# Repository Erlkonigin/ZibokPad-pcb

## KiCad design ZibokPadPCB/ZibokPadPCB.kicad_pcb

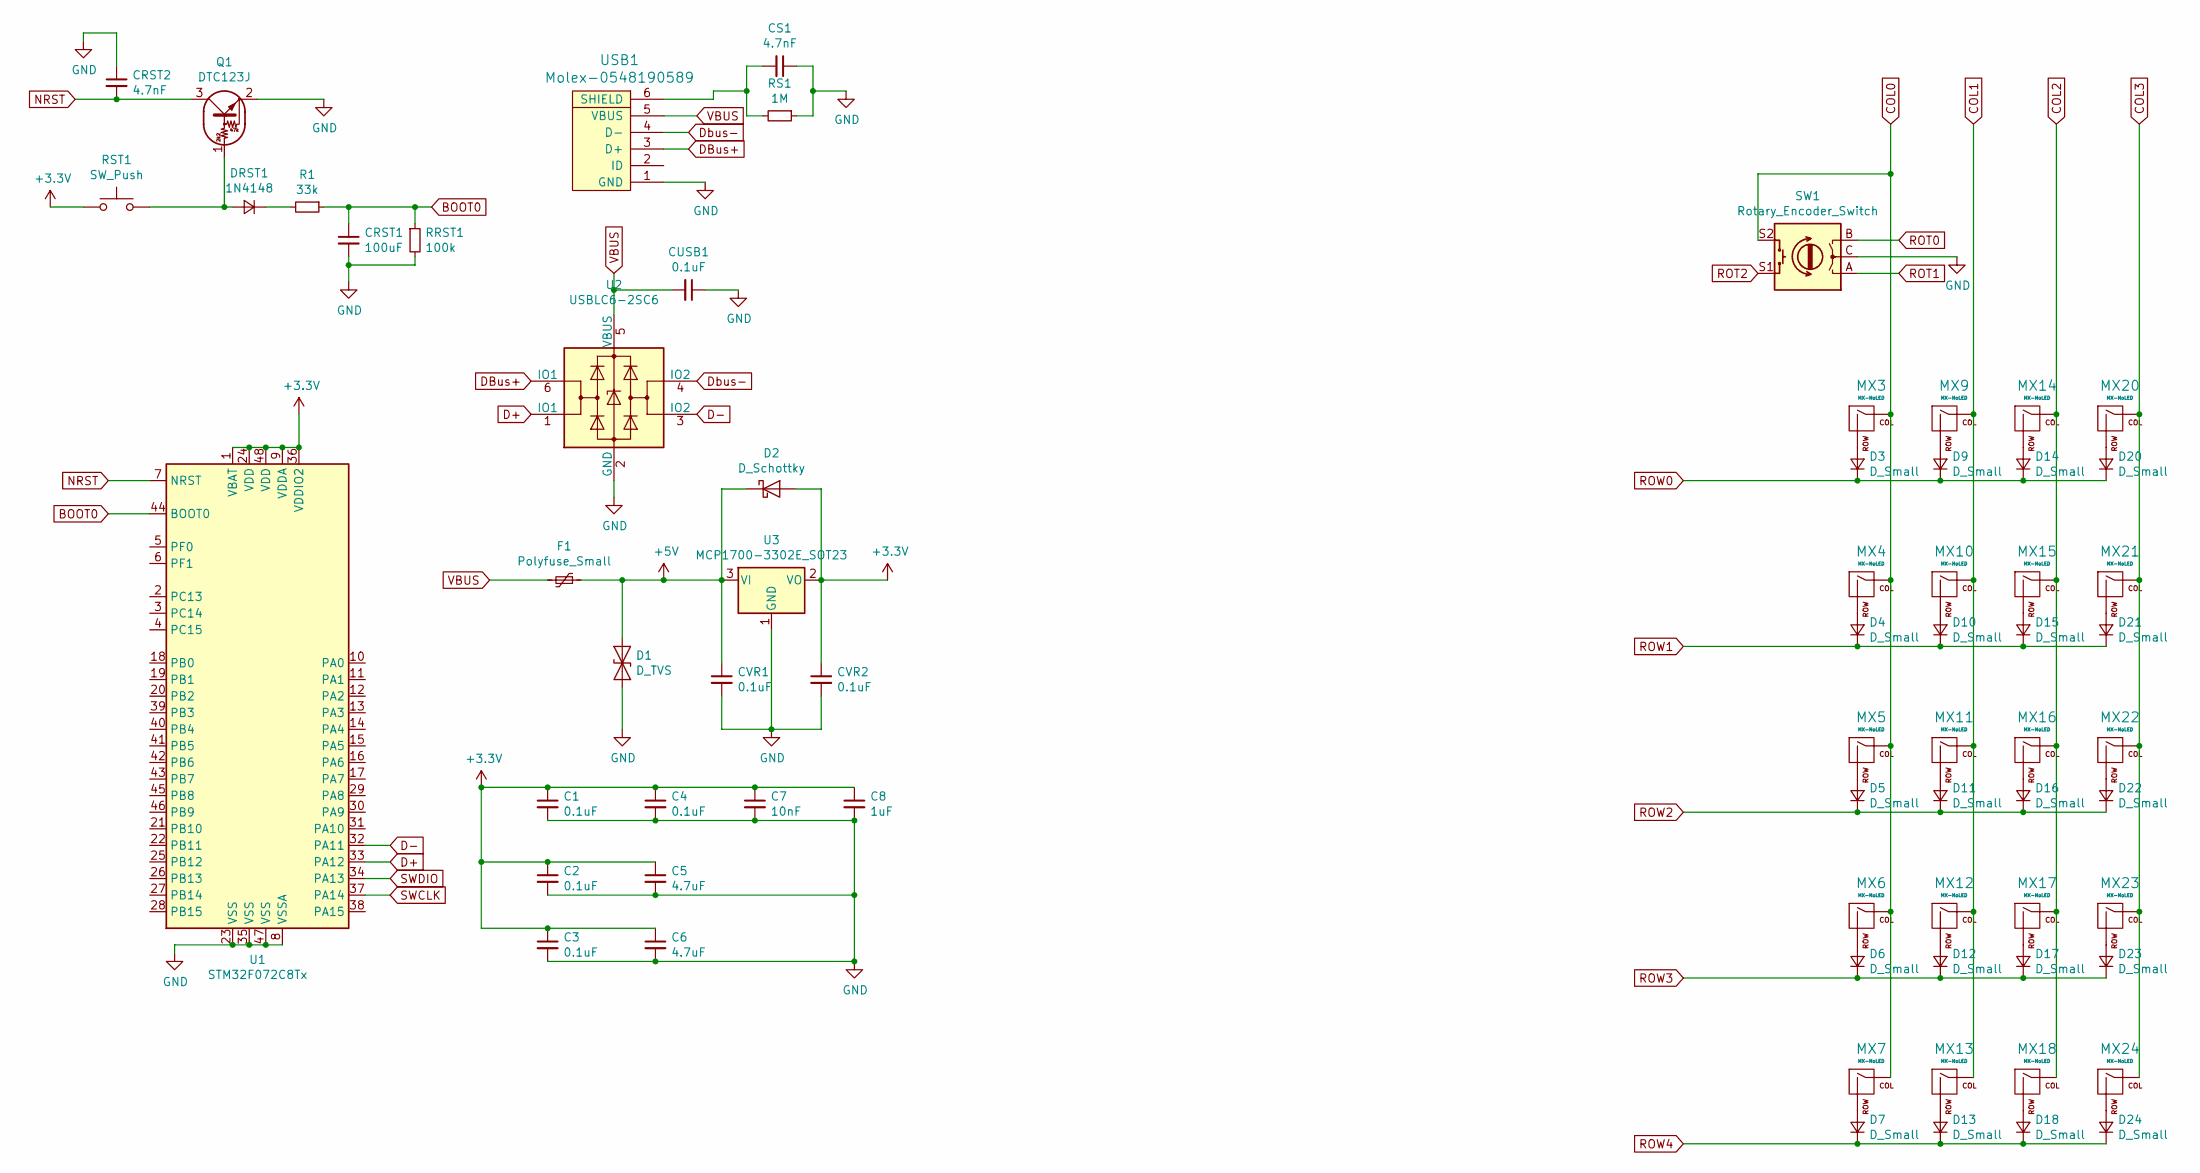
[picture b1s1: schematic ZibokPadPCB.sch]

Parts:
C1, C2, C3, C4: 0.1uF; C_0805_2012Metric
C5, C6: 4.7uF; C_0805_2012Metric
C7: 10nF; C_0805_2012Metric
C8: 1uF; C_0805_2012Metric
CRST1: 100uF; C_0805_2012Metric
CRST2: 4.7nF; C_0805_2012Metric
CS1: 4.7nF; C_0805_2012Metric
CUSB1: 0.1uF; C_0805_2012Metric
CVR1, CVR2: 0.1uF; C_0805_2012Metric
D1: D_TVS; D_SOD-123
D2: D_Schottky; D_SOD-123
D3, D4, D5, D6, D7, D9, D10, D11, D12, D13, D14, D15, D16, D17, D18, D20, D21, D22, D23, D24: D_Small; D_SOD-123
DRST1: 1N4148; D_SOD-123
F1: Polyfuse_Small; Fuse_1206_3216Metric
MX3, MX4, MX5, MX6, MX7, MX9, MX10, MX11, MX12, MX13, MX14, MX15, MX16, MX17, MX18, MX20, MX21, MX22, MX23, MX24: MX-NoLED; MXOnly-1U-NoLED
Q1: DTC123J; SOT-523
R1: 33k; R_0805_2012Metric
RRST1: 100k; R_0805_2012Metric
RS1: 1M; R_0805_2012Metric
RST1: SW_Push; SKQG-1155865
SW1: Rotary_Encoder_Switch; RotaryEncoder_Alps_EC11E-Switch_Vertical_H20mm
U1: STM32F072C8Tx; LQFP-48_7x7mm_P0.5mm
U2: USBLC6-2SC6; SOT-23-6
U3: MCP1700-3302E_SOT23; SOT-23
USB1: Molex-0548190589

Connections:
+3V3: C1.1, C2.1, C3.1, C4.1, C5.1, C6.1, C7.1, C8.1, CVR2.1, D2.2 (A), RST1.1, U1.1 (VBAT), U1.9 (VDDA), U1.24 (VDD), U1.36 (VDDIO2), U1.48 (VDD), U3.2 (VO)
+5V: CVR1.1, D1.1 (A1), D2.1 (K), F1.1, U3.3 (VI)
BOOT0: CRST1.1, R1.1, RRST1.1, U1.44 (BOOT0)
COL0: MX3.1 (COL), MX4.1 (COL), MX5.1 (COL), MX6.1 (COL), MX7.1 (COL), SW1.S2, U1.22 (PB11)
COL1: MX9.1 (COL), MX10.1 (COL), MX11.1 (COL), MX12.1 (COL), MX13.1 (COL), U1.21 (PB10)
COL2: MX14.1 (COL), MX15.1 (COL), MX16.1 (COL), MX17.1 (COL), MX18.1 (COL), U1.20 (PB2)
COL3: MX20.1 (COL), MX21.1 (COL), MX22.1 (COL), MX23.1 (COL), MX24.1 (COL), U1.19 (PB1)
D+: U1.33 (PA12), U2.1 (IO1)
D-: U1.32 (PA11), U2.3 (IO2)
DBus+: U2.6 (IO1), USB1.3 (D+)
Dbus-: U2.4 (IO2), USB1.4 (D-)
GND: C1.2, C2.2, C3.2, C4.2, C5.2, C6.2, C7.2, C8.2, CRST1.2, CRST2.1, CS1.1, CUSB1.1, CVR1.2, CVR2.2, D1.2 (A2), Q1.2 (E), RRST1.2, RS1.1, SW1.C, U1.8 (VSSA), U1.23 (VSS), U1.35 (VSS), U1.47 (VSS), U2.2 (GND), U3.1 (GND), USB1.1 (GND)
NRST: CRST2.2, Q1.3 (C), U1.7 (NRST)
unnamed: CS1.2, RS1.2, USB1.6 (SHIELD)
unnamed: D3.2 (A), MX3.2 (ROW)
unnamed: D4.2 (A), MX4.2 (ROW)
unnamed: D5.2 (A), MX5.2 (ROW)
unnamed: D6.2 (A), MX6.2 (ROW)
unnamed: D7.2 (A), MX7.2 (ROW)
unnamed: D9.2 (A), MX9.2 (ROW)
unnamed: D10.2 (A), MX10.2 (ROW)
unnamed: D11.2 (A), MX11.2 (ROW)
unnamed: D12.2 (A), MX12.2 (ROW)
unnamed: D13.2 (A), MX13.2 (ROW)
unnamed: D14.2 (A), MX14.2 (ROW)
unnamed: D15.2 (A), MX15.2 (ROW)
unnamed: D16.2 (A), MX16.2 (ROW)
unnamed: D17.2 (A), MX17.2 (ROW)
unnamed: D18.2 (A), MX18.2 (ROW)
unnamed: D20.2 (A), MX20.2 (ROW)
unnamed: D21.2 (A), MX21.2 (ROW)
unnamed: D22.2 (A), MX22.2 (ROW)
unnamed: D23.2 (A), MX23.2 (ROW)
unnamed: D24.2 (A), MX24.2 (ROW)
unnamed: DRST1.1 (K), R1.2
unnamed: DRST1.2 (A), Q1.1 (B), RST1.2
ROT0: SW1.B
ROT1: SW1.A
ROT2: SW1.S1
ROW0: D3.1 (K), D9.1 (K), D14.1 (K), D20.1 (K), U1.43 (PB7)
ROW1: D4.1 (K), D10.1 (K), D15.1 (K), D21.1 (K), U1.42 (PB6)
ROW2: D5.1 (K), D11.1 (K), D16.1 (K), D22.1 (K), U1.41 (PB5)
ROW3: D6.1 (K), D12.1 (K), D17.1 (K), D23.1 (K), U1.40 (PB4)
ROW4: D7.1 (K), D13.1 (K), D18.1 (K), D24.1 (K), U1.39 (PB3)
SWCLK: U1.37 (PA14)
SWDIO: U1.34 (PA13)
VBUS: CUSB1.2, F1.2, U2.5 (VBUS), USB1.5 (VBUS)

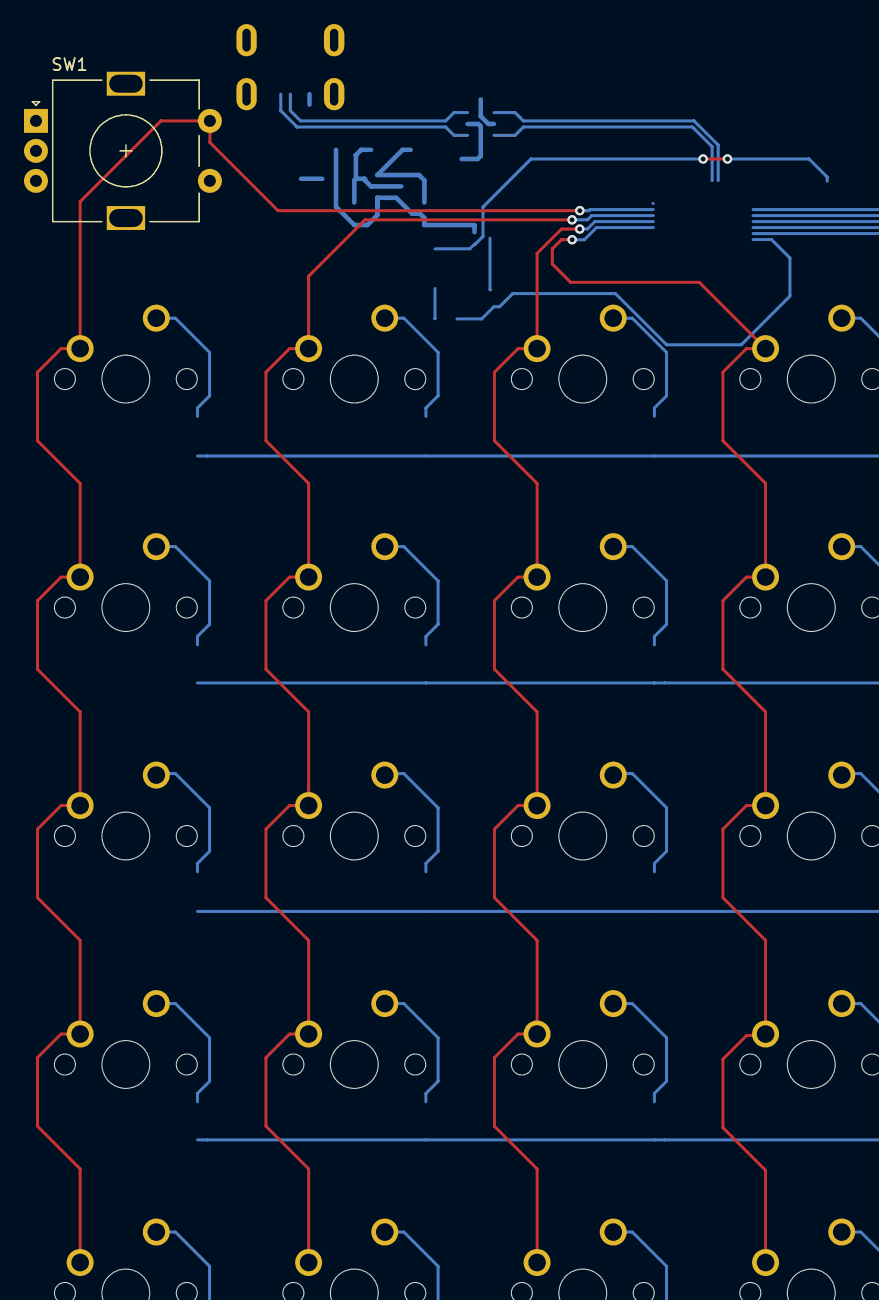
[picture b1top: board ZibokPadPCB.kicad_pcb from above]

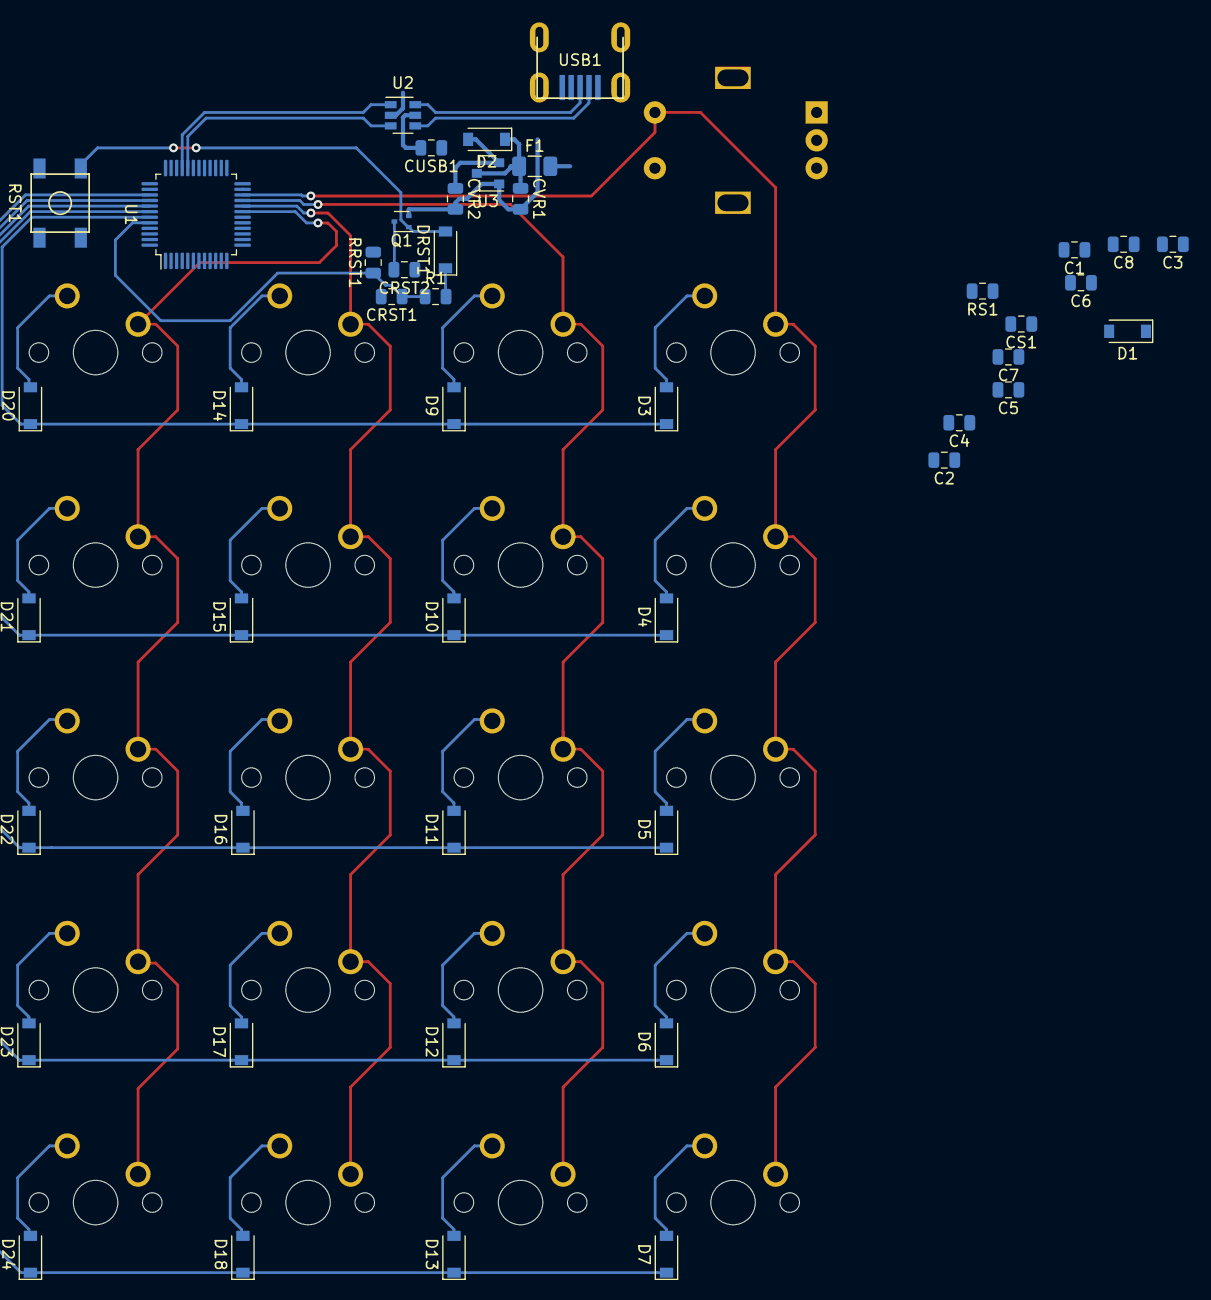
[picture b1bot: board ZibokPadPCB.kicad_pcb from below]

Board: 2 copper layers, 68 parts (47 on the bottom side), 42 nets.

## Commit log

2020-07-24 Added submodules
2020-07-24 started project
2020-07-24 Enabled libraries
2020-07-24 MCU schematic complete
2020-07-24 Key schematic finish
2020-07-24 Continuation
2020-07-25 Switched to stm32
2020-07-25 Started routing
2020-07-25 routing
2020-07-25 led work start
